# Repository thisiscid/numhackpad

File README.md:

# numhackpad

numhackpad is a 16 key macropad with nothing else except for cool oneshot art

## Features:
- 16 keys
- cool oneshot reference on the pcb

## CAD Model:
the case and pcb should fit nicely with 8 m3 screws and heatset inserts. 4 for the case, 4 for the PCB (standoffs).

it has 2 printed pieces: the bottom and the top of the case

made using Fusion360

## PCB
heres the pcb, it was made using KiCAD and the silkscreen was taken from a google image of the oneshot lightbulb (no spoilers!)
schematic

pcb

used cherry MX for the footprints

## Firmware Overview
numhackpad uses [KMK](https://github.com/KMKfw) firmware.

- the 16 keys act as a numpad, it is missing the delete key

## BOM:
here should be everything you need to make this hackpad

- 16x Cherry MX Switches
- 16x DSA Keycaps
- 8x M3x5x4 Heatset inserts
- 8x M3x16mm screws
- 16x 1N4148 DO-35 Diodes.
- 1x XIAO RP2040
- 1x Case (2 printed parts)
- 1x PCB

## Extra stuff
lwk it started off as a normal hackpad and then got a lot worse

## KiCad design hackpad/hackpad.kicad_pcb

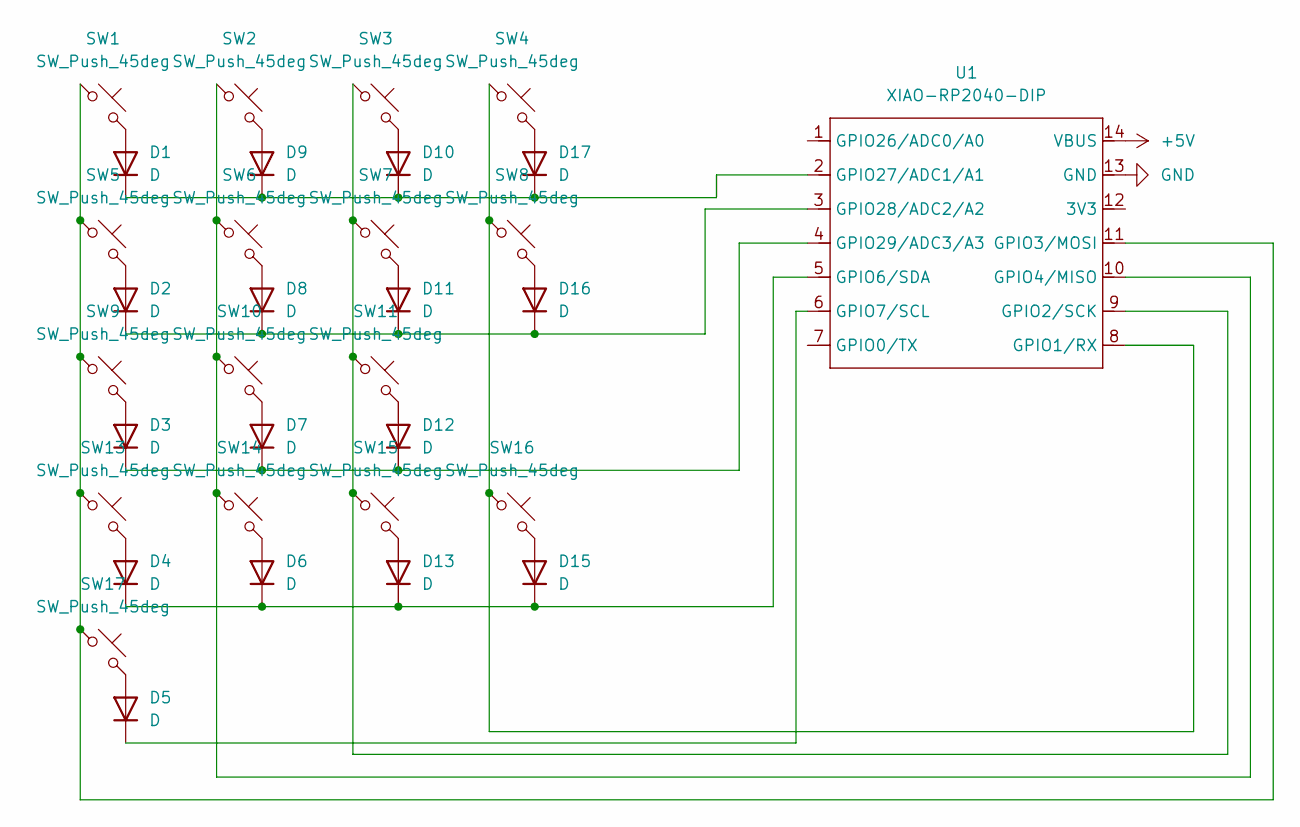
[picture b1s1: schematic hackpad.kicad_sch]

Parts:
D1, D2, D3, D4, D5, D6, D7, D8, D9, D10, D11, D12, D13, D15, D16, D17: D; D_DO-35_SOD27_P7.62mm_Horizontal
SW1, SW2, SW3, SW4, SW5, SW6, SW7, SW9, SW10, SW11, SW13, SW14, SW15: SW_Push_45deg; SW_Cherry_MX_1.00u_PCB
SW8, SW16: SW_Push_45deg; SW_Cherry_MX_2.00u_Vertical_PCB
SW17: SW_Push_45deg; SW_Cherry_MX_2.00u_PCB
U1: XIAO-RP2040-DIP

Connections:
+5V: U1.14 (VBUS)
GND: U1.13 (GND)
unnamed: D1.2 (A), SW1.2
unnamed: D1.1 (K), D9.1 (K), D10.1 (K), D17.1 (K), U1.2 (GPIO27/ADC1/A1)
unnamed: D2.2 (A), SW5.2
unnamed: D3.2 (A), SW9.2
unnamed: D4.2 (A), SW13.2
unnamed: D5.2 (A), SW17.2
unnamed: D5.1 (K), U1.6 (GPIO7/SCL)
unnamed: D6.2 (A), SW14.2
unnamed: D7.2 (A), SW10.2
unnamed: D8.2 (A), SW6.2
unnamed: D9.2 (A), SW2.2
unnamed: D10.2 (A), SW3.2
unnamed: D11.2 (A), SW7.2
unnamed: D2.1 (K), D8.1 (K), D11.1 (K), D16.1 (K), U1.3 (GPIO28/ADC2/A2)
unnamed: D12.2 (A), SW11.2
unnamed: D3.1 (K), D7.1 (K), D12.1 (K), U1.4 (GPIO29/ADC3/A3)
unnamed: D13.2 (A), SW15.2
unnamed: D4.1 (K), D6.1 (K), D13.1 (K), D15.1 (K), U1.5 (GPIO6/SDA)
unnamed: D15.2 (A), SW16.2
unnamed: D16.2 (A), SW8.2
unnamed: D17.2 (A), SW4.2
unnamed: SW4.1, SW8.1, SW16.1, U1.8 (GPIO1/RX)
unnamed: SW3.1, SW7.1, SW11.1, SW15.1, U1.9 (GPIO2/SCK)
unnamed: SW1.1, SW5.1, SW9.1, SW13.1, SW17.1, U1.11 (GPIO3/MOSI)
unnamed: SW2.1, SW6.1, SW10.1, SW14.1, U1.10 (GPIO4/MISO)

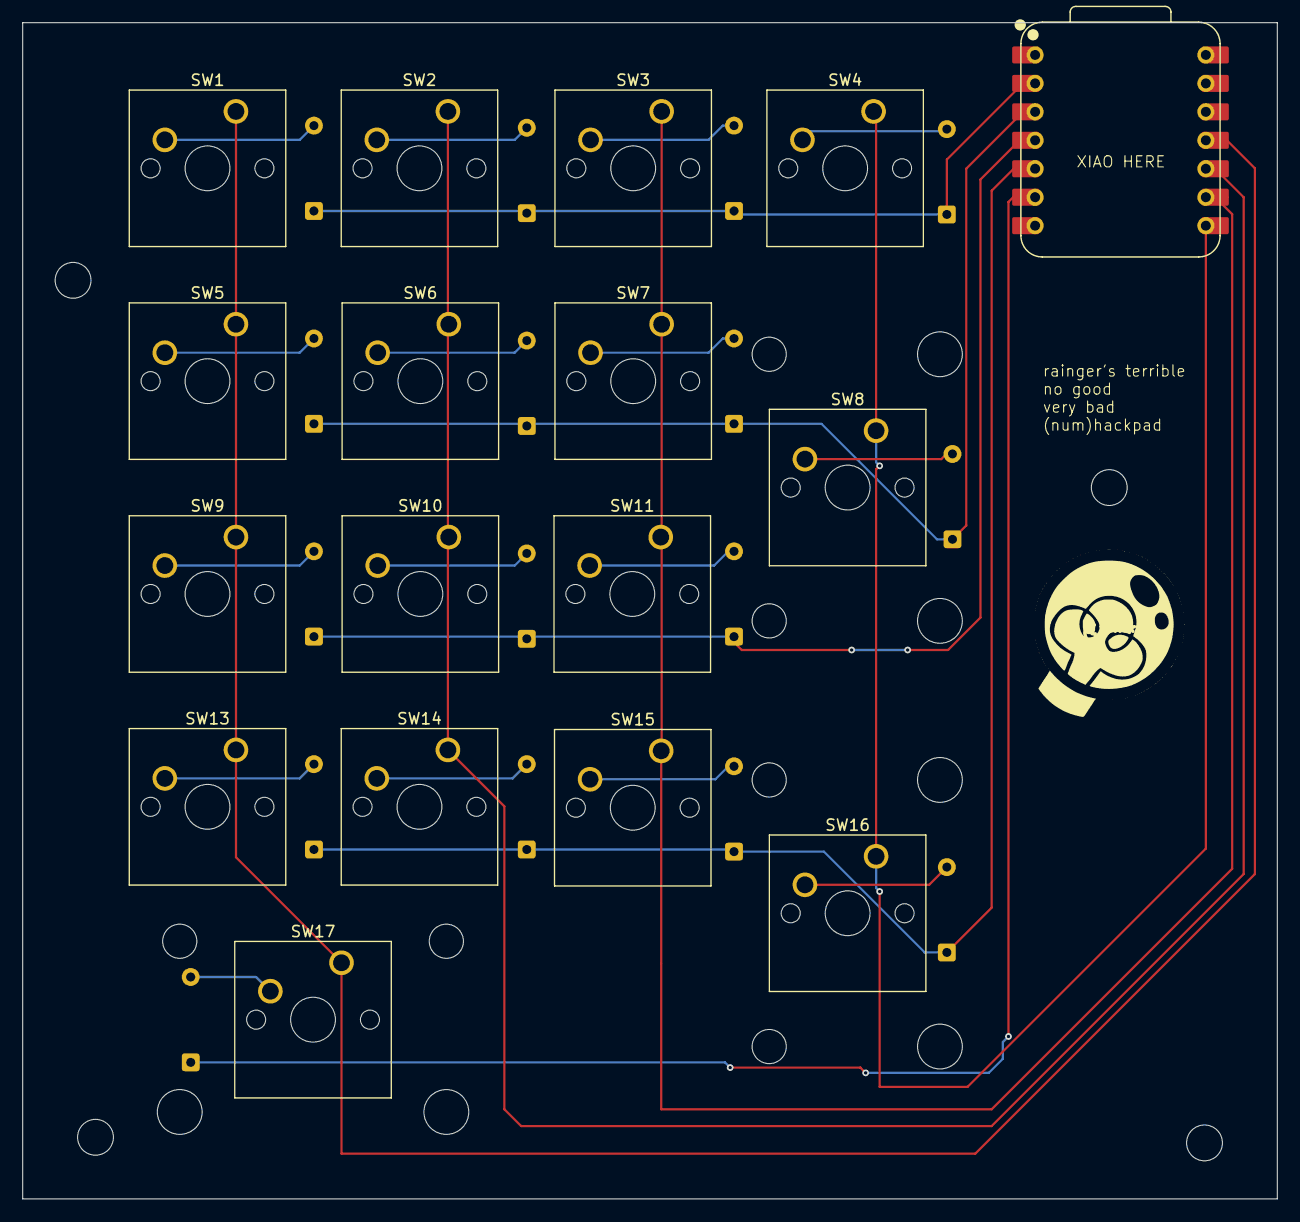
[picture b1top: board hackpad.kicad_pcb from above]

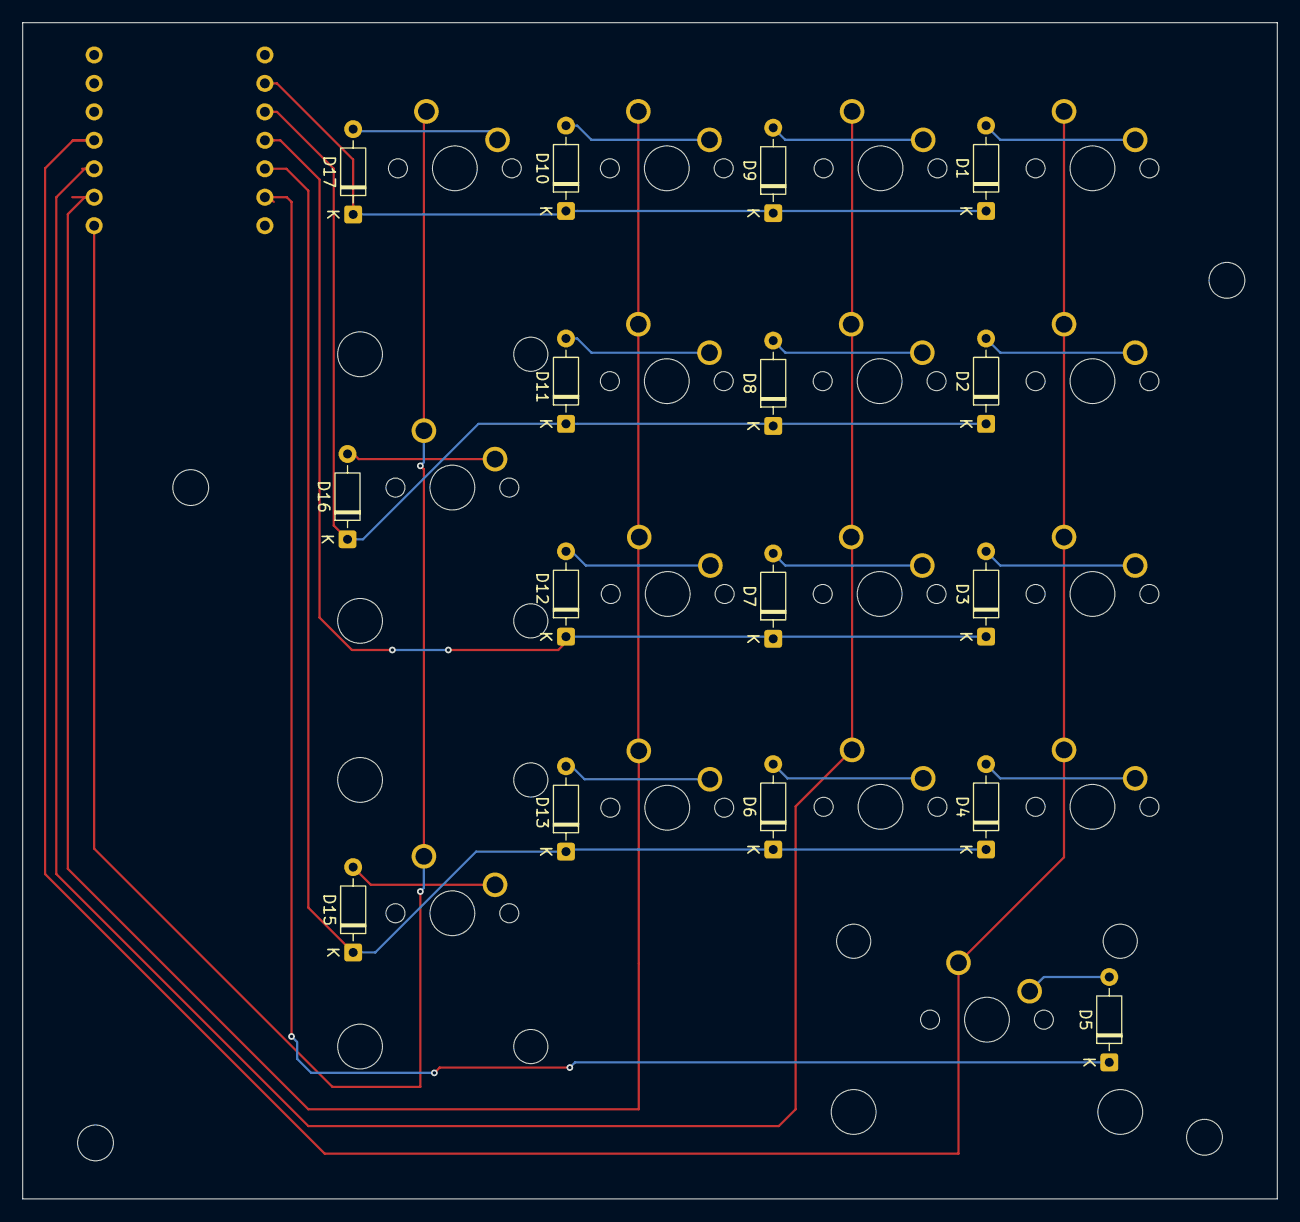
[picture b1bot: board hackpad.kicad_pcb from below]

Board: 2 copper layers, 112.0 x 105.0 mm, 33 parts (16 on the bottom side), 25 nets.

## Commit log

2025-07-03 make journal.md
2025-07-04 JOURNAL.md stuff, did more work on the pcb (including just completely changing what i was originally doing)
2025-07-04 oops forgot hours spent...
2025-07-04 minor formatting error ugh
2025-07-04 more jouirnal, more changing stuff, also .DS_Store to gitignore
2025-07-06 more hackpad stuff! woo!
2025-07-06 adding the step file
2025-07-06 add all the files, start with firmware
2025-07-06 start working on the firmware
2025-07-06 new journal entry!
2025-07-06 final update, just a main.py thing where i moved it round (also, changed up the pin order bcs i accidentally did it wrong)
2025-07-06 oops actually forgot to remove macros as well oopsie
2025-07-06 orginization, README
2025-07-06 oops forgot to change the name :3
2025-07-06 another minor change
2025-07-06 updated the 3d model to add keycaps and also made one slot a bit bigger, updated the journal, updated images in readme
2025-07-06 update to add a cool highway banner :33
